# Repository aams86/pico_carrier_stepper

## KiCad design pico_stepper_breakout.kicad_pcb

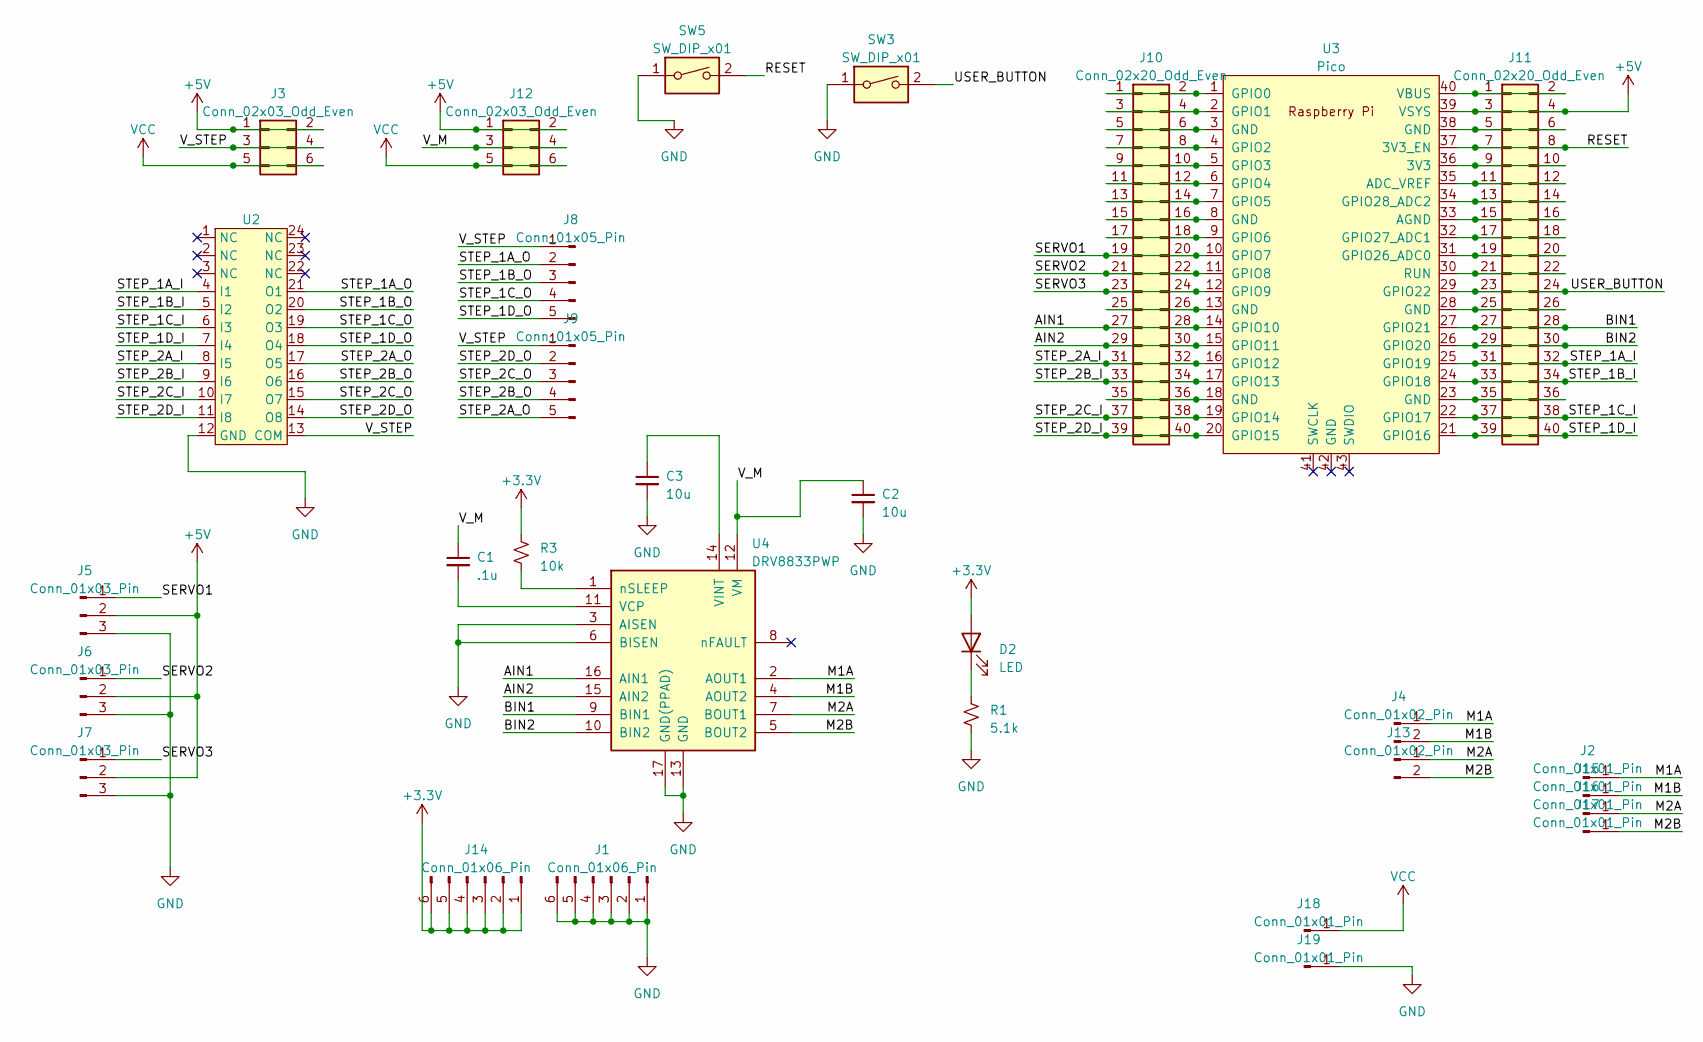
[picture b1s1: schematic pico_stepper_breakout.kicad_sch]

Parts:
C1: .1u; C_0603_1608Metric; JLCPCB C14663
C2, C3: 10u; C_0805_2012Metric; JLCPCB C15850
D2: LED; LED_0805_2012Metric; JLCPCB C2297
J1, J14: Conn_01x06_Pin; PinSocket_1x06_P2.54mm_Vertical; JLCPCB C40877
J2, J15, J16, J17, J18, J19: Conn_01x01_Pin; TestPoint_Keystone_5019_Minature
J3, J12: Conn_02x03_Odd_Even; PinHeader_2x03_P2.54mm_Vertical; JLCPCB C65114
J4, J13: Conn_01x02_Pin; JST_XH_B2B-XH-A_1x02_P2.50mm_Vertical
J5, J6, J7: Conn_01x03_Pin; PinHeader_1x03_P2.54mm_Vertical; JLCPCB C49257
J8, J9: Conn_01x05_Pin; JST_XH_B5B-XH-AM_1x05_P2.50mm_Vertical; JLCPCB C161872
J10, J11: Conn_02x20_Odd_Even; PinHeader_2x20_P2.54mm_Vertical_SMD; JLCPCB C3975165
R1: 5.1k; R_0402_1005Metric; JLCPCB C25905
R3: 10k; R_0402_1005Metric; JLCPCB C25744
SW3, SW5: SW_DIP_x01; SW_SPST_TL3305C; JLCPCB C5340160
U2: SSOP-24_3.9x8.7mm_P0.635mm
U3: Pico; RPi_Pico_SMD_TH
U4: DRV8833PWP; HTSSOP-16-1EP_4.4x5mm_P0.65mm_EP3.4x5mm_Mask2.46x2.31mm_The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; JLCPCB C50506

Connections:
+3.3V: D2.2 (A), J14.1, J14.2, J14.3, J14.4, J14.5, J14.6, R3.1
+5V: J3.1, J3.2, J5.2, J6.2, J7.2, J11.3, J11.4, J12.1, J12.2, U3.39 (VSYS)
/AIN1: J10.27, J10.28, U3.14 (GPIO10), U4.16 (AIN1)
/AIN2: J10.29, J10.30, U3.15 (GPIO11), U4.15 (AIN2)
/BIN1: J11.27, J11.28, U3.27 (GPIO21), U4.9 (BIN1)
/BIN2: J11.29, J11.30, U3.26 (GPIO20), U4.10 (BIN2)
/M1A: J2.1, J4.1, U4.2 (AOUT1)
/M1B: J4.2, J15.1, U4.4 (AOUT2)
/M2A: J13.1, J16.1, U4.7 (BOUT1)
/M2B: J13.2, J17.1, U4.5 (BOUT2)
/RESET: J11.7, J11.8, SW5.2, U3.37 (3V3_EN)
/SERVO1: J5.1, J10.19, J10.20, U3.10 (GPIO7)
/SERVO2: J6.1, J10.21, J10.22, U3.11 (GPIO8)
/SERVO3: J7.1, J10.23, J10.24, U3.12 (GPIO9)
/STEP_1A_I: J11.31, J11.32, U2.4 (I1), U3.25 (GPIO19)
/STEP_1A_O: J8.2, U2.21 (O1)
/STEP_1B_I: J11.33, J11.34, U2.5 (I2), U3.24 (GPIO18)
/STEP_1B_O: J8.3, U2.20 (O2)
/STEP_1C_I: J11.37, J11.38, U2.6 (I3), U3.22 (GPIO17)
/STEP_1C_O: J8.4, U2.19 (O3)
/STEP_1D_I: J11.39, J11.40, U2.7 (I4), U3.21 (GPIO16)
/STEP_1D_O: J8.5, U2.18 (O4)
/STEP_2A_I: J10.31, J10.32, U2.8 (I5), U3.16 (GPIO12)
/STEP_2A_O: J9.5, U2.17 (O5)
/STEP_2B_I: J10.33, J10.34, U2.9 (I6), U3.17 (GPIO13)
/STEP_2B_O: J9.4, U2.16 (O6)
/STEP_2C_I: J10.37, J10.38, U2.10 (I7), U3.19 (GPIO14)
/STEP_2C_O: J9.3, U2.15 (O7)
/STEP_2D_I: J10.39, J10.40, U2.11 (I8), U3.20 (GPIO15)
/STEP_2D_O: J9.2, U2.14 (O8)
/USER_BUTTON: J11.23, J11.24, SW3.2, U3.29 (GPIO22)
/V_M: C1.1, C2.1, J12.3, J12.4, U4.12 (VM)
/V_STEP: J3.3, J3.4, J8.1, J9.1, U2.13 (COM)
GND: C2.2, C3.2, J1.1, J1.2, J1.3, J1.4, J1.5, J1.6, J5.3, J6.3, J7.3, J19.1, R1.2, SW3.1, SW5.1, U2.12 (GND), U4.3 (AISEN), U4.6 (BISEN), U4.13 (GND), U4.17 (GND(PPAD))
unnamed: D2.1 (K), R1.1
unnamed: J10.1, J10.2, U3.1 (GPIO0)
unnamed: J10.3, J10.4, U3.2 (GPIO1)
unnamed: J10.5, J10.6, U3.3 (GND)
unnamed: J10.7, J10.8, U3.4 (GPIO2)
unnamed: J10.9, J10.10, U3.5 (GPIO3)
unnamed: J10.11, J10.12, U3.6 (GPIO4)
unnamed: J10.13, J10.14, U3.7 (GPIO5)
unnamed: J10.15, J10.16, U3.8 (GND)
unnamed: J10.17, J10.18, U3.9 (GPIO6)
unnamed: J10.25, J10.26, U3.13 (GND)
unnamed: J10.35, J10.36, U3.18 (GND)
unnamed: J11.1, J11.2, U3.40 (VBUS)
unnamed: J11.5, J11.6, U3.38 (GND)
unnamed: J11.9, J11.10, U3.36 (3V3)
unnamed: J11.11, J11.12, U3.35 (ADC_VREF)
unnamed: J11.13, J11.14, U3.34 (GPIO28_ADC2)
unnamed: J11.15, J11.16, U3.33 (AGND)
unnamed: J11.17, J11.18, U3.32 (GPIO27_ADC1)
unnamed: J11.19, J11.20, U3.31 (GPIO26_ADC0)
unnamed: J11.21, J11.22, U3.30 (RUN)
unnamed: J11.25, J11.26, U3.28 (GND)
unnamed: J11.35, J11.36, U3.23 (GND)
unnamed: C1.2, U4.11 (VCP)
unnamed: C3.1, U4.14 (VINT)
unnamed: R3.2, U4.1 (nSLEEP)
VCC: J3.5, J3.6, J12.5, J12.6, J18.1

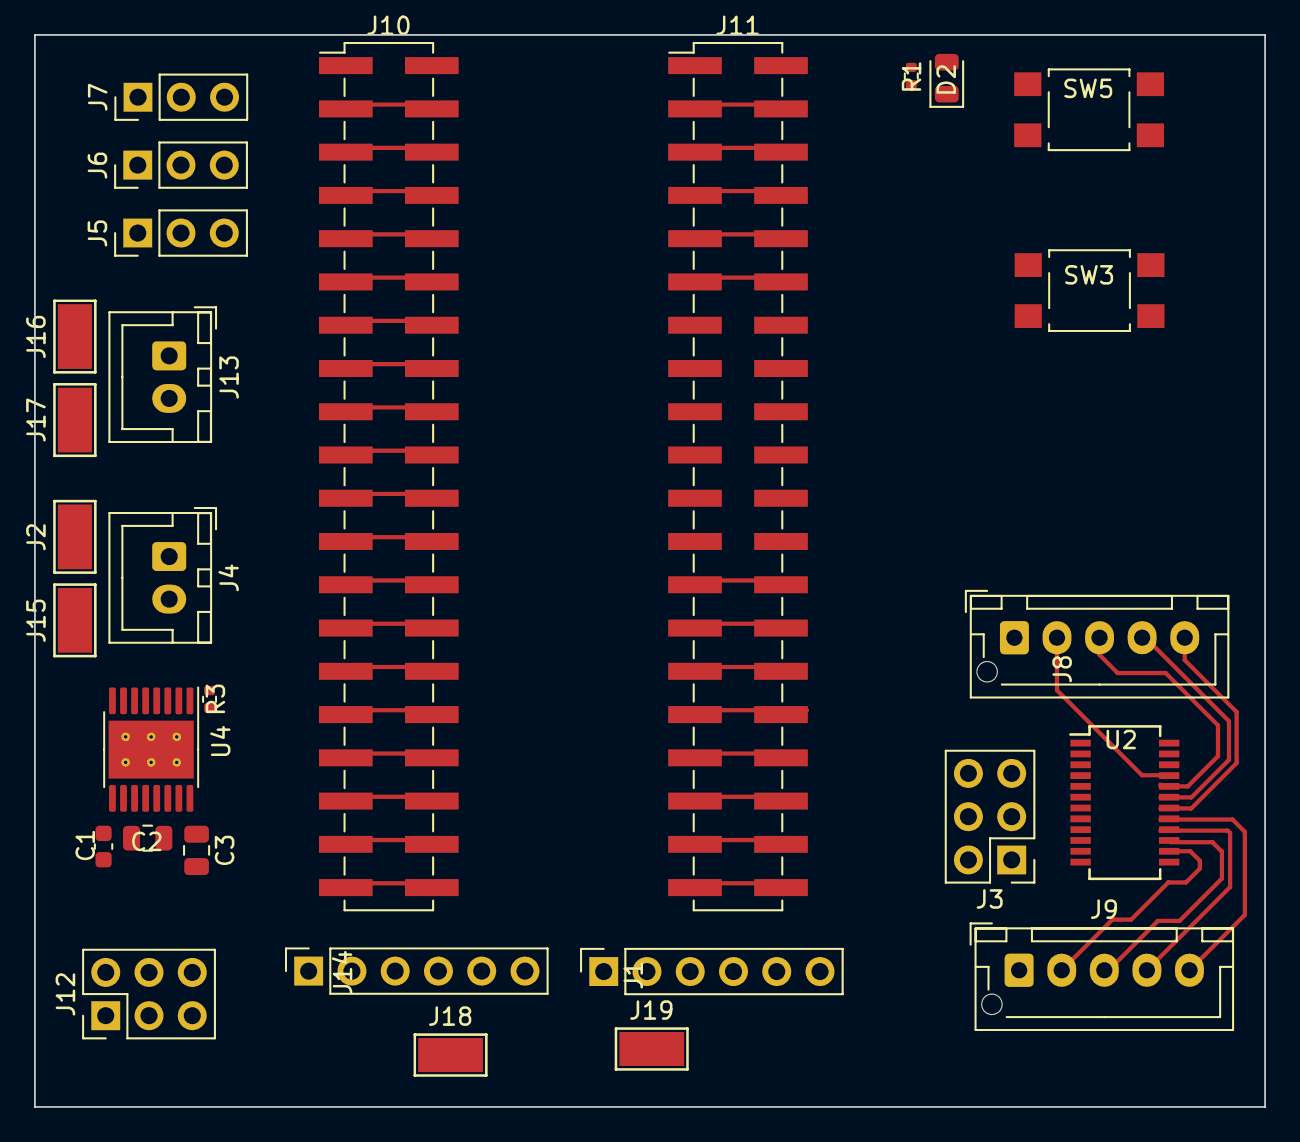
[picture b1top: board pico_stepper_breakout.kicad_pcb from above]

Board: 2 copper layers, 72.2 x 62.9 mm, 29 parts (0 on the bottom side), 61 nets.
